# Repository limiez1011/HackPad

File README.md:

# CADPad
12 switch macropad with a rotary encoder and  .91" oled screen.

## Bill of Materials
- 12x MX Style Switches
- 4x M3x5mx4mm heatset inserts
- 3D Printed case
- 4x M3x16mm screws
- 12x Blank DSA keycaps
- 1x seeed studios xiao rp2040 sma version
- 1x 0.91" oled screen
- 1x EC11 rotary encoder
- 12x Through-hole 1N4148 Diodes
- 1x knob

## Usecase
Id like to use the hackpad for fusion shortcuts to make 3d design easier.

# PHOTOS

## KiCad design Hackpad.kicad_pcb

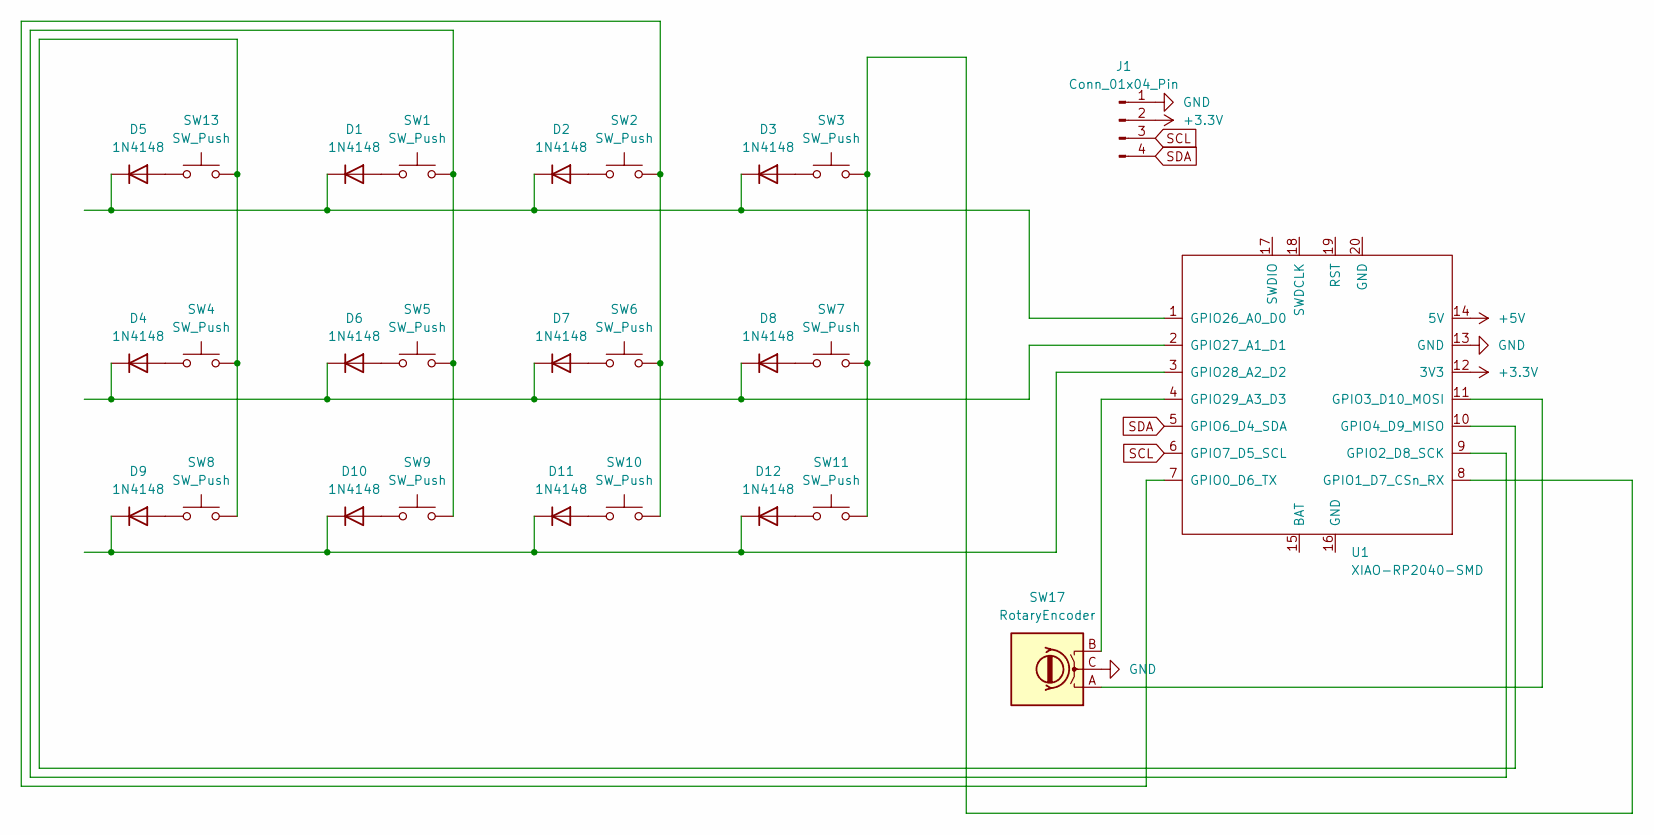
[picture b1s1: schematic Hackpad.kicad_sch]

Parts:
D1, D2, D3, D4, D5, D6, D7, D8, D9, D10, D11, D12: 1N4148; D_DO-35_SOD27_P7.62mm_Horizontal
J1: Conn_01x04_Pin; SSD1306-0.91-OLED-4pin-128x32
SW1, SW2, SW3, SW4, SW5, SW6, SW7, SW8, SW9, SW10, SW11, SW13: SW_Push; SW_Cherry_MX_1.00u_PCB
SW17: RotaryEncoder; RotaryEncoder_Alps_EC11E-Switch_Vertical_H20mm
U1: XIAO-RP2040-SMD

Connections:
+3.3V: J1.2, U1.12 (3V3)
+5V: U1.14 (5V)
GND: J1.1, SW17.C, U1.13 (GND)
unnamed: D1.2 (A), SW1.1
unnamed: D1.1 (K), D2.1 (K), D3.1 (K), D5.1 (K), U1.1 (GPIO26_A0_D0)
unnamed: D2.2 (A), SW2.1
unnamed: D3.2 (A), SW3.1
unnamed: D4.2 (A), SW4.1
unnamed: D4.1 (K), D6.1 (K), D7.1 (K), D8.1 (K), U1.2 (GPIO27_A1_D1)
unnamed: D5.2 (A), SW13.1
unnamed: D6.2 (A), SW5.1
unnamed: D7.2 (A), SW6.1
unnamed: D8.2 (A), SW7.1
unnamed: D9.2 (A), SW8.1
unnamed: D10.2 (A), SW9.1
unnamed: D9.1 (K), D10.1 (K), D11.1 (K), D12.1 (K), U1.3 (GPIO28_A2_D2)
unnamed: D11.2 (A), SW10.1
unnamed: D12.2 (A), SW11.1
unnamed: SW2.2, SW6.2, SW10.2, U1.7 (GPIO0_D6_TX)
unnamed: SW3.2, SW7.2, SW11.2, U1.8 (GPIO1_D7_CSn_RX)
unnamed: SW1.2, SW5.2, SW9.2, U1.9 (GPIO2_D8_SCK)
unnamed: SW17.A, U1.11 (GPIO3_D10_MOSI)
unnamed: SW4.2, SW8.2, SW13.2, U1.10 (GPIO4_D9_MISO)
unnamed: SW17.B, U1.4 (GPIO29_A3_D3)
SCL: J1.3, U1.6 (GPIO7_D5_SCL)
SDA: J1.4, U1.5 (GPIO6_D4_SDA)

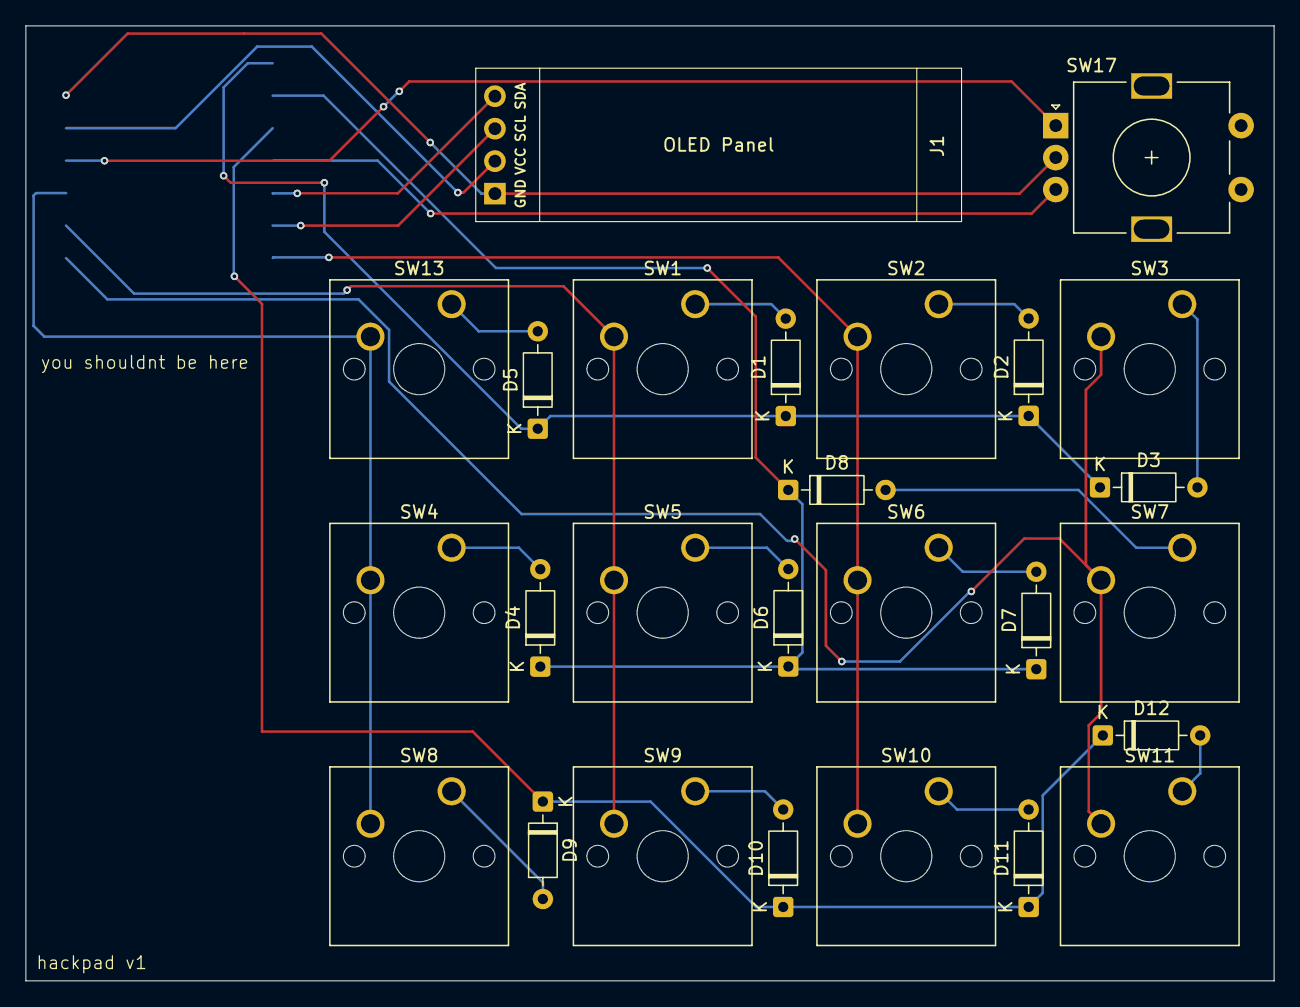
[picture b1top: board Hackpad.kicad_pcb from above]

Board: 2 copper layers, 97.6 x 74.7 mm, 27 parts (1 on the bottom side), 25 nets.

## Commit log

2026-01-31 Create x
2026-01-31 Kicad files
2026-01-31 Create xx
2026-01-31 Case and full cad model
2026-01-31 Create o
2026-01-31 Update README with correct RP2040 version
2026-01-31 Rename HackPad to CADPad in README
2026-01-31 Revise Bill of Materials in README
    Updated Bill of Materials with correct item descriptions and formatting.
2026-01-31 Add knob to components list in README
    Added a knob to the list of components.
